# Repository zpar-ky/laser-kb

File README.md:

# Laser-85
### A GMK Laser inspired case, in a custom 85-key handwired ortholinear package.

## the plan  

Design and print case with http://builder.swillkb.com/, steel switchplate cut by Lasergist, acrylic cut by Ponoko.    
Philosophy for layers is the ability to only have to use one hand while using modifiers.  

| Layer | Type   | Material       | Width |
|:-----:|:------:|:--------------:|:-----:|
|   1   | Switch | Steel          | 1.5mm |
|   2   | Closed | Purple Acrylic | ~3mm  |
|   3   | Open   | Purple Acrylic | ~3mm  |
|   4   | Open   | Blue Acrylic   | ~4mm  |
|   5   | Closed | Purple Acrylic | ~3mm  |
|   6   | Closed | Purple Acrylic | ~3mm  |
|   7   | Bottom | Blue Acrylic   | ~4mm  |
|       |        | Total Inside   | ~13mm |
|       |        | Total          | ~20mm |

swillkb settings:  

underside design:  

## programming  
Teensy 2.0 planned pinout: (going from top left down)  
B1, B2, B3, B7, D0, D1, D2, D3, D5, C6, C7, D5, D7, B4, B5, B6, F7, F6, F5, F4, F1, F0  
gives 22 pins for 17x5 matrix  
Build with http://kbfirmware.com/ as base and then edit the rest according to qmk standards

Itemlist
------

| Item           | Product name          | Price   | Link                                                  | Comments               |
|:---------------|:---------------------:|:-------:|:-----------------------------------------------------:|:-----------------------|
| Switches       | Gateron blacks        | $24.99  | [link](https://www.massdrop.com/buy/gateron-switches) | Bought from massdrop   |
| Diodes         | 1N4148 diode          | $5.99   | [link](https://www.amazon.com/gp/product/B06XB1R2NK)  | 300pcs                 |
| Insulated Wire | Striveday 22AWG       | $7.99   | [link](https://www.amazon.com/gp/product/B01IBAIL60)  | 5m purple              |
| Solder         | Sywon 60/40           | $7.99   | [link](https://www.amazon.com/gp/product/B01LVTTL9E)  | 0.039" dia, 50g        |
| Soldering Tool | Sywon 60w kit         | $32.99  | [link](https://www.amazon.com/gp/product/B01N4571Q6)  | includes temp control  |
| Wire Stripper  | Irwin Vise-Grip       | $10.70  | [link](https://www.amazon.com/gp/product/B000JNNWQ2)  |                        |
| Spacers        | M2/M3 Brass Standoffs | $14.99  | [link](https://www.amazon.com/gp/product/B00MNG2T6W)  | yeah this was overkill |
| Screws         | Rion Tech Screw Kit   | $9.99   | [link](https://www.amazon.com/gp/product/B072NZY69F)  | similarly overkill     |
| USB Extender   | YCS Basics Mini-B M-F | $7.99   | [link](https://www.amazon.com/gp/product/B01CKMGD10)  |                        |
| Controller     | Teensy 2.0            | $20.95  | [link](https://www.amazon.com/gp/product/B00NC43256)  |                        |
| Switch plate   | Cut by lasergist      | $81.34  | [link](https://www.lasergist.com)                     | they ship from Greece  |
| Acrylics       | Cut by ponoko         | $91.07  | [link](https://www.ponoko.com)                        | first shot             |
| Acrylics       | Cut by ponoko         | $54.92  | [link](https://www.ponoko.com)                        | second shot            |
| Keycap Set     | GMK Laser             | $??.??  | [link](https://www.massdrop.com/talk/455/laser-gmk)   |                        |
| Total          |                       | $371.9  |                                                       | not including caps yet |

Total would be less if tools are already owned, and also some items (like 300 pack of diodes) aren't used in entirety and the real cost is less

Final thoughts
------

## guides used  
https://www.reddit.com/r/MechanicalKeyboards/comments/4l0p41/guide_detailed_guide_to_making_a_custom_keyboard/  
https://github.com/qmk/qmk_firmware/blob/0787d70e55a668244445d9328f3cda2303cc6877/docs/hand_wire.md  
https://github.com/ruiqimao/keyboard-pcb-guide

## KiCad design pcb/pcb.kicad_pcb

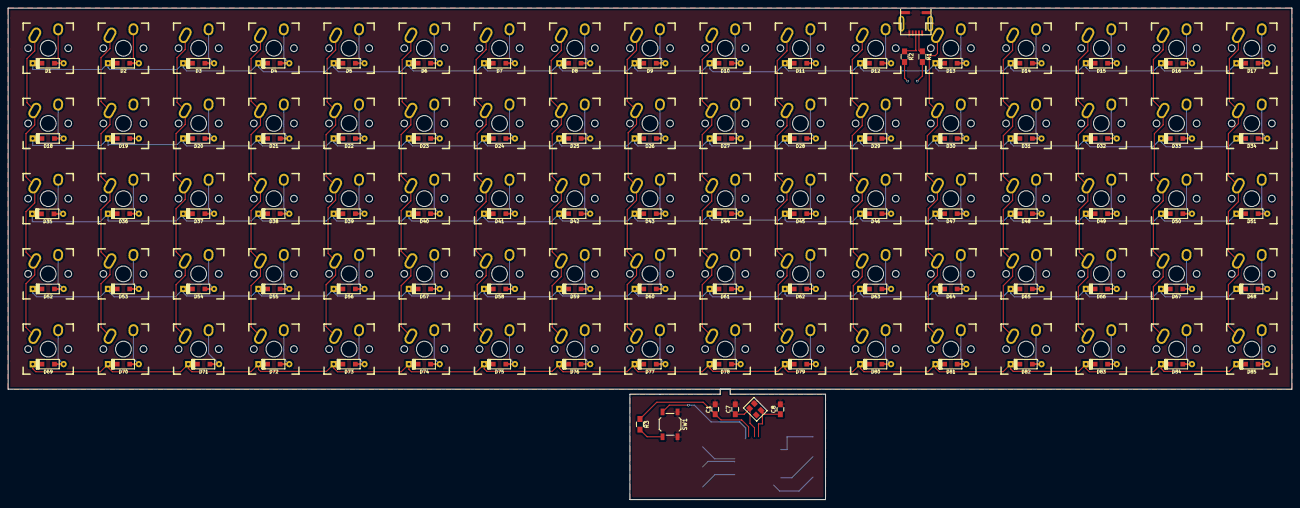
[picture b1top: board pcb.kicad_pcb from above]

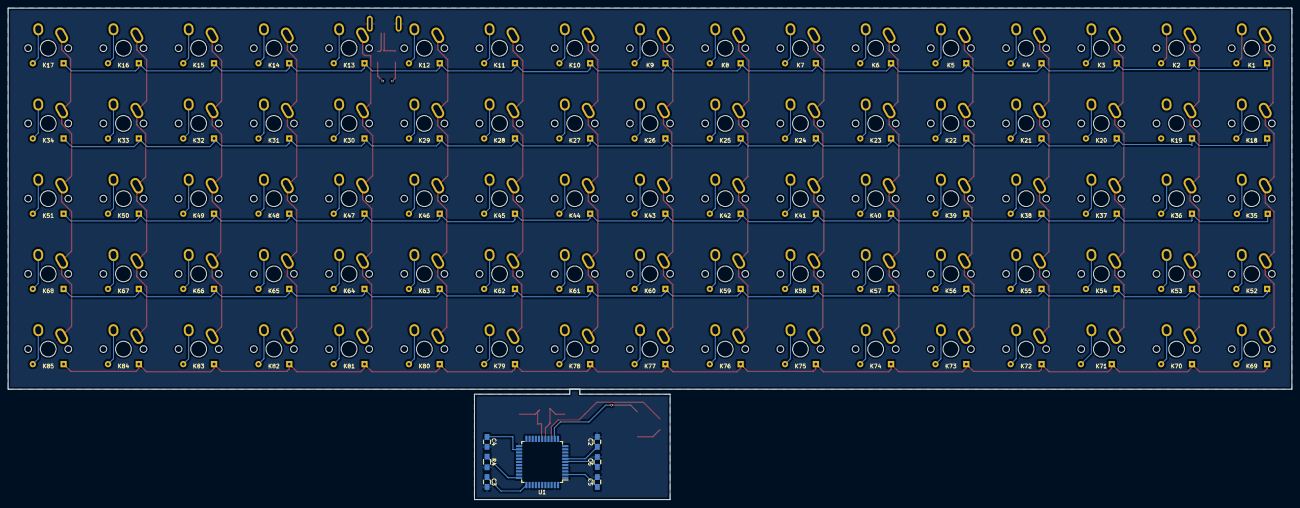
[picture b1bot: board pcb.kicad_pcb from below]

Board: 2 copper layers, 325.1 x 124.5 mm, 186 parts (7 on the bottom side), 118 nets.

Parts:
C1, C2, C3, C4: 0.1u; C_0805_HandSoldering
C5: 4.7u; C_0805_HandSoldering
C6: 1u; C_0805_HandSoldering
C7, C8: 22p; C_0805_HandSoldering
D1, D2, D3, D4, D5, D6, D7, D8, D9, D10, D11, D12, D13, D14, D15, D16, D17, D18, D19, D20, D21, D22, D23, D24, D25, D26, D27, D28, D29, D30, D31, D32, D33, D34, D35, D36, D37, D38, D39, D40, D41, D42, D43, D44, D45, D46, D47, D48, D49, D50, D51, D52, D53, D54, D55, D56, D57, D58, D59, D60, D61, D62, D63, D64, D65, D66, D67, D68, D69, D70, D71, D72, D73, D74, D75, D76, D77, D78, D79, D80, D81, D82, D83, D84, D85: D; D_SOD123_axial
J1: USB_mini_micro_B; USB_miniB_hirose_5S8
K1, K2, K3, K4, K5, K6, K7, K8, K9, K10, K11, K12, K13, K14, K15, K16, K17, K18, K19, K20, K21, K22, K23, K24, K25, K26, K27, K28, K29, K30, K31, K32, K33, K34, K35, K36, K37, K38, K39, K40, K41, K42, K43, K44, K45, K46, K47, K48, K49, K50, K51, K52, K53, K54, K55, K56, K57, K58, K59, K60, K61, K62, K63, K64, K65, K66, K67, K68, K69, K70, K71, K72, K73, K74, K75, K76, K77, K78, K79, K80, K81, K82, K83, K84, K85: KEYSW; Mx_Alps_100
R1, R2: 22; R_0805_HandSoldering
R3, R4: 10k; R_0805_HandSoldering
SW1: SW_PUSH; SW_SPST_TL3342
U1: ATMEGA32U4; LQFP-44_10x10mm_Pitch0.8mm
X1: XTAL_GND; FA-238

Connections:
/row0: D1.1, D2.1, D3.1, D4.1, D5.1, D6.1, D7.1, D8.1, D9.1, D10.1, D11.1, D12.1, D13.1, D14.1, D15.1, D16.1, D17.1
/row1: D18.1, D19.1, D20.1, D21.1, D22.1, D23.1, D24.1, D25.1, D26.1, D27.1, D28.1, D29.1, D30.1, D31.1, D32.1, D33.1, D34.1
/row2: D35.1, D36.1, D37.1, D38.1, D39.1, D40.1, D41.1, D42.1, D43.1, D44.1, D45.1, D46.1, D47.1, D48.1, D49.1, D50.1, D51.1
/row3: D52.1, D53.1, D54.1, D55.1, D56.1, D57.1, D58.1, D59.1, D60.1, D61.1, D62.1, D63.1, D64.1, D65.1, D66.1, D67.1, D68.1
/row4: D69.1, D70.1, D71.1, D72.1, D73.1, D74.1, D75.1, D76.1, D77.1, D78.1, D79.1, D80.1, D81.1, D82.1, D83.1, D84.1, D85.1
GND: C1.2, C2.2, C3.2, C4.2, C5.2, C6.2, C7.2, C8.2, J1.5, J1.6, R4.2, SW1.1, U1.5, U1.15, U1.23, U1.35, U1.43, X1.3
unnamed: C6.1, U1.6
unnamed: C7.1, U1.16, X1.1
unnamed: C8.1, U1.17, X1.2
unnamed: D1.2, K1.2
unnamed: D2.2, K2.2
unnamed: D3.2, K3.2
unnamed: D4.2, K4.2
unnamed: D5.2, K5.2
unnamed: D6.2, K6.2
unnamed: D7.2, K7.2
unnamed: D8.2, K8.2
unnamed: D9.2, K9.2
unnamed: D10.2, K10.2
unnamed: D11.2, K11.2
unnamed: D12.2, K12.2
unnamed: D13.2, K13.2
unnamed: D14.2, K14.2
unnamed: D15.2, K15.2
unnamed: D16.2, K16.2
unnamed: D17.2, K17.2
unnamed: D18.2, K18.2
unnamed: D19.2, K19.2
unnamed: D20.2, K20.2
unnamed: D21.2, K21.2
unnamed: D22.2, K22.2
unnamed: D23.2, K23.2
unnamed: D24.2, K24.2
unnamed: D25.2, K25.2
unnamed: D26.2, K26.2
unnamed: D27.2, K27.2
unnamed: D28.2, K28.2
unnamed: D29.2, K29.2
unnamed: D30.2, K30.2
unnamed: D31.2, K31.2
unnamed: D32.2, K32.2
unnamed: D33.2, K33.2
unnamed: D34.2, K34.2
unnamed: D35.2, K35.2
unnamed: D36.2, K36.2
unnamed: D37.2, K37.2
unnamed: D38.2, K38.2
unnamed: D39.2, K39.2
unnamed: D40.2, K40.2
unnamed: D41.2, K41.2
unnamed: D42.2, K42.2
unnamed: D43.2, K43.2
unnamed: D44.2, K44.2
unnamed: D45.2, K45.2
unnamed: D46.2, K46.2
unnamed: D47.2, K47.2
unnamed: D48.2, K48.2
unnamed: D49.2, K49.2
unnamed: D50.2, K50.2
unnamed: D51.2, K51.2
unnamed: D52.2, K52.2
unnamed: D53.2, K53.2
unnamed: D54.2, K54.2
unnamed: D55.2, K55.2
unnamed: D56.2, K56.2
unnamed: D57.2, K57.2
unnamed: D58.2, K58.2
unnamed: D59.2, K59.2
unnamed: D60.2, K60.2
unnamed: D61.2, K61.2
unnamed: D62.2, K62.2
unnamed: D63.2, K63.2
unnamed: D64.2, K64.2
unnamed: D65.2, K65.2
unnamed: D66.2, K66.2
unnamed: D67.2, K67.2
unnamed: D68.2, K68.2
unnamed: D69.2, K69.2
unnamed: D70.2, K70.2
unnamed: D71.2, K71.2
unnamed: D72.2, K72.2
unnamed: D73.2, K73.2
unnamed: D74.2, K74.2
unnamed: D75.2, K75.2
unnamed: D76.2, K76.2
unnamed: D77.2, K77.2
unnamed: D78.2, K78.2
unnamed: D79.2, K79.2
unnamed: D80.2, K80.2
unnamed: D81.2, K81.2
unnamed: D82.2, K82.2
unnamed: D83.2, K83.2
unnamed: D84.2, K84.2
unnamed: D85.2, K85.2
unnamed: J1.2, R1.1
unnamed: J1.3, R2.1
unnamed: K1.1, K18.1, K35.1, K52.1, K69.1
unnamed: K10.1, K27.1, K44.1, K61.1, K78.1
unnamed: K11.1, K28.1, K45.1, K62.1, K79.1
unnamed: K12.1, K29.1, K46.1, K63.1, K80.1
unnamed: K13.1, K30.1, K47.1, K64.1, K81.1
unnamed: K14.1, K31.1, K48.1, K65.1, K82.1
unnamed: K15.1, K32.1, K49.1, K66.1, K83.1
unnamed: K16.1, K33.1, K50.1, K67.1, K84.1
unnamed: K17.1, K34.1, K51.1, K68.1, K85.1
unnamed: K2.1, K19.1, K36.1, K53.1, K70.1
unnamed: K3.1, K20.1, K37.1, K54.1, K71.1
unnamed: K4.1, K21.1, K38.1, K55.1, K72.1
unnamed: K5.1, K22.1, K39.1, K56.1, K73.1
unnamed: K6.1, K23.1, K40.1, K57.1, K74.1
unnamed: K7.1, K24.1, K41.1, K58.1, K75.1
unnamed: K8.1, K25.1, K42.1, K59.1, K76.1
unnamed: K9.1, K26.1, K43.1, K60.1, K77.1
unnamed: R1.2, U1.3
unnamed: R2.2, U1.4
unnamed: R3.2, SW1.2, U1.13
unnamed: R4.1, U1.33
VCC: C1.1, C2.1, C3.1, C4.1, C5.1, J1.1, R3.1, U1.2, U1.7, U1.14, U1.24, U1.34, U1.44

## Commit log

2017-08-01 Add kbfirmware files
2017-08-01 Layout change
2017-08-01 Update keymap
    going to be hand coding the keymap from now on, not using kbfirmware. Changed keymap format from kbfirmware to qmk standards
2017-08-01 Added _FUNCT Layer
    Base layer with the 'Fn' key now goes to layer 3 which has Fn10 through Fn24
2017-08-02 Add other keyboard layouts
    haha ten million changed files
2017-08-03 Added PCB files
2017-08-04 Updated PCB
    added tracks for all the switches (whew!)
2017-08-04 Updated PCB
    pcb is unfinished and will need serious tuneups to get it off the ground, if I ever do so
2017-08-04 add asset gitignore to reduce files
2017-08-04 excellent job gitignore please do your job
2017-08-04 can't do gitignore after files are already uploaded
    shut up
2017-08-04 don't worry about it
2017-08-04 Update README.md
    whew
2017-08-04 Removed QMK Files
    also update readme.md :^)
2017-08-04 removed some pcb files
2017-08-10 Update and fix qmk config + hex files
2017-08-10 update to fit my garbage wiring
2017-08-10 nevermind this one might be the one that worked for me idk
2017-08-10 uppdate hex file for new layout
2017-08-10 update keymap
